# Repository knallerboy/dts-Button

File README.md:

<!-- PROJECT LOGO -->

# dts-Button

damn, that smart button

## how to build?

  - HTC Vive Tracker is needed
  - print the attached stl file
  - useful but not essential: use a JST connector

  solder your button on a PCB with the two terminals from the JST connector (or you solder the wire directly),
  solder the wires to your designated pogo pin on the adapter plate of the Tracker

## Built With

  - Soldiworks, Blender
  - KiCad

## Result

## thank you
  - thanks to: https://www.mocapfusion.com/
  - looking for help? https://discord.com/invite/ErZcKaQ @LineByLine
    
<br />

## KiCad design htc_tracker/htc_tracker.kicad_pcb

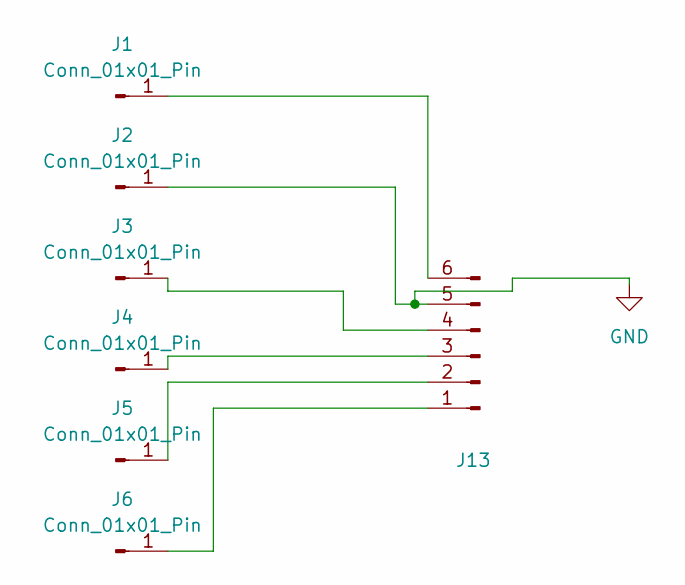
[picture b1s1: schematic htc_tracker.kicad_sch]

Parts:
J1, J2, J3, J4, J5, J6: Conn_01x01_Pin; SolderWirePad_1x01_SMD_1x2mm
J13: Conn_01x06_Pin; PinHeader_1x06_P2.54mm_Vertical

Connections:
GND: J2.1, J13.5
unnamed: J1.1, J13.6
unnamed: J6.1, J13.1
unnamed: J5.1, J13.2
unnamed: J4.1, J13.3
unnamed: J3.1, J13.4

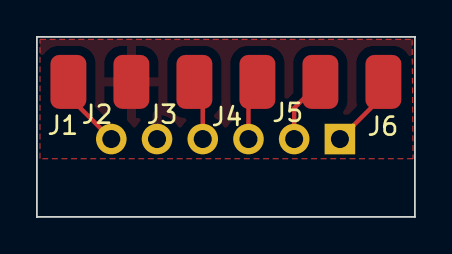
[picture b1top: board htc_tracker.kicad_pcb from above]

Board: 2 copper layers, 21.0 x 10.0 mm, 7 parts (1 on the bottom side), 6 nets.

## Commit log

2023-10-29 README.md
2023-10-29 Create files
